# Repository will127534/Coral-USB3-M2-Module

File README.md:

# Coral M.2 Module with USB3 connection with Host

Basically this is a 2242 M.2 Module with VL805 PCIe to USB3 controller connected to Google Coral Module via USB3, because Google Coral TPU still has some issue with the PCIe Driver on Raspberry Pi 4 as of 2022/09.

PCB designed with KiCad v6.0

More details (Blog post?) here: [Coral USB3 M2 Module](https://www.willwhang.dev/coral-USB3-M2-Module/)

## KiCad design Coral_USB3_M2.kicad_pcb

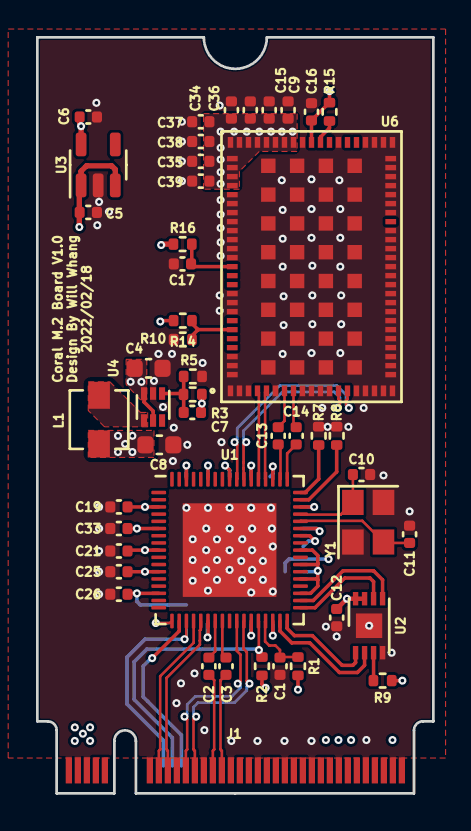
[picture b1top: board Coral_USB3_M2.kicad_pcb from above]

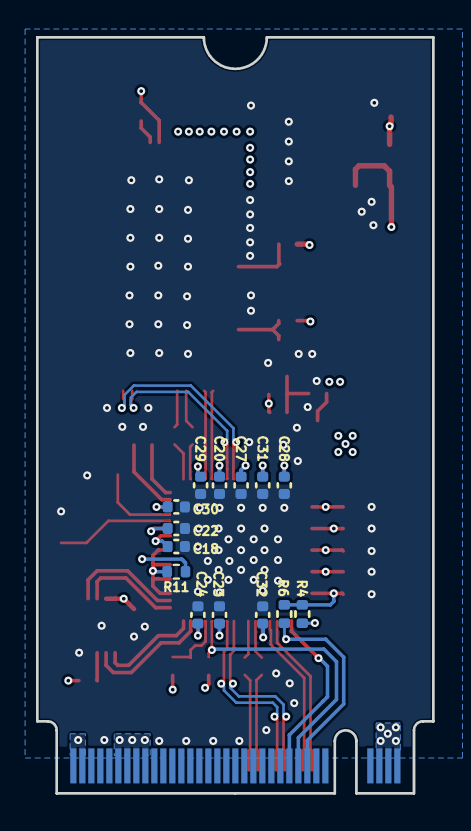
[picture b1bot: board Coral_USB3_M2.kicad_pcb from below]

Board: 4 copper layers, 22.0 x 42.0 mm, 61 parts (14 on the bottom side), 40 nets.

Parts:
C1, C16: 1uF; C_0402_1005Metric
C2, C3, C12, C13, C14, C15, C17, C18, C19, C20, C21, C22, C23, C24, C25, C26, C27, C28, C29, C30, C31, C32, C33, C34, C35, C36, C37, C38, C39: 100nF; C_0402_1005Metric
C4: 10uF; C_0603_1608Metric
C5, C6, C9: 10uF; C_0402_1005Metric
C7: 10pF; C_0402_1005Metric
C8: 22uF; C_0603_1608Metric
C10, C11: 18pF; C_0402_1005Metric
J1: Bus_M.2_Socket_M; NGFF_M
L1: 1uH; L_Vishay_IHLP-1212
R1, R2, R6, R9, R16: 10K; R_0402_1005Metric
R3: 75K; R_0402_1005Metric
R4, R10: DNP; R_0402_1005Metric
R5: 100K; R_0402_1005Metric
R7: 4.7K; R_0402_1005Metric
R8: 6.04K; R_0402_1005Metric
R11: 15K; R_0402_1005Metric
R14: 0R; R_0402_1005Metric
R15: 1K; R_0402_1005Metric
U1: VL805; QFN-68-1EP_8x8mm_P0.4mm_EP5.2x5.2mm
U2: W25Q32JVZP; DFN-8-1EP_3x2mm_P0.5mm_EP1.36x1.46mm
U3: AP2204K-1.8; SOT-23-5
U4: TLV62568ADRLR; SOT-563
U6: G313-06329-00; MODULE_G313-06329-00
Y1: 25Mhz; Crystal_SMD_3225-4Pin_3.2x2.5mm

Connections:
+1V1: C7.1, C8.1, C18.2, C19.2, C21.2, C23.2, C25.2, C27.2, C29.2, C31.2, L1.2, R3.1, U1.3 (VCCA10SSRX34), U1.9 (VDD), U1.12 (VCCA10SSRX34), U1.29 (VDD), U1.45 (VDD), U1.54 (VCCA10SSRX12), U1.60 (VDD), U1.63 (VCCA10SSRX12)
+1V8: C6.1, C16.1, R14.2, R15.2, R16.1, U3.5 (VOUT), U6.54 (AON)
+3.3VA: C4.2, C5.1, C9.1, C12.2, C15.1, C20.2, C22.2, C24.2, C26.2, C28.2, C30.2, C32.2, C33.2, C34.2, C35.2, C36.2, C37.2, C38.2, C39.2, J1.2 (3.3V), J1.4 (3.3V), J1.12 (3.3V), J1.14 (3.3V), J1.16 (3.3V), J1.18 (3.3V), J1.70 (3.3V), J1.72 (3.3V), J1.74 (3.3V), R1.2, R2.2, R4.2, R6.2, R9.1, R11.2, U1.6 (VCCA33SS34), U1.15 (VCCA33SS34), U1.23 (VCCA33PEX), U1.32 (VSUS33), U1.46 (VSUS33), U1.49 (VCCA33SSM), U1.57 (VCCA33SS12), U1.66 (VCCA33SS12), U2.7 (IO3), U2.8 (VCC), U3.1 (VIN), U3.3 (EN), U4.3 (VIN), U4.5 (EN), U6.56 (VIN), U6.57 (VIN), U6.58 (VIN), U6.59 (VIN), U6.60 (VIN), U6.61 (VIN), U6.62 (VIN), U6.63 (VIN), U6.64 (VIN), U6.65 (VIN), U6.66 (VIN), U6.67 (VIN)
GND: C1.1, C4.1, C5.2, C6.2, C8.2, C9.2, C10.1, C11.1, C12.1, C15.2, C16.2, C17.2, C18.1, C19.1, C20.1, C21.1, C22.1, C23.1, C24.1, C25.1, C26.1, C27.1, C28.1, C29.1, C30.1, C31.1, C32.1, C33.1, C34.1, C35.1, C36.1, C37.1, C38.1, C39.1, J1.1 (GND), J1.3 (GND), J1.9 (GND), J1.15 (GND), J1.21 (GND), J1.27 (GND), J1.33 (GND), J1.39 (GND), J1.45 (GND), J1.51 (GND), J1.57 (GND), J1.71 (GND), J1.73 (GND), J1.75 (GND), R5.2, R7.1, R8.1, R10.1, U1.69 (GND), U2.4 (GND), U2.9 (EP), U3.2 (GND), U4.2 (GND), U6.1 (GND), U6.2 (GND), U6.3 (GND), U6.6 (GND), U6.9 (GND), U6.10 (PCIE_REFCLK_N), U6.11 (PCIE_REFCLK_P), U6.12 (GND), U6.15 (GND), U6.16 (GND), U6.17 (GND), U6.18 (GND), U6.19 (GND), U6.20 (GND), U6.21 (GND), U6.22 (GND), U6.23 (GND), U6.24 (GND), U6.25 (GND), U6.26 (GND), U6.27 (GND), U6.28 (GND), U6.29 (GND), U6.30 (GND), U6.31 (GND), U6.32 (GND), U6.33 (GND), U6.34 (GND), U6.35 (GND), U6.36 (GND), U6.38 (GND), U6.39 (GND), U6.40 (GND), U6.41 (GND), U6.42 (GND), U6.43 (GND), U6.44 (GND), U6.45 (GND), U6.46 (GND), U6.47 (GND), U6.48 (GND), U6.51 (GND), U6.55 (GND), U6.68 (GND), U6.69 (GND), U6.70 (GND), U6.71 (GND), U6.72 (GND), U6.73 (GND), U6.74 (GND), U6.75 (GND), U6.79 (GND), U6.80 (GND), U6.81 (GND), U6.86 (GND), U6.87 (GND), U6.88 (GND), U6.89 (GND), U6.90 (GND), U6.91 (GND), U6.92 (GND), U6.93 (GND), U6.94 (GND), U6.95 (GND), U6.96 (GND), U6.97 (GND), U6.98 (GND), U6.99 (GND), U6.100 (GND), U6.101 (GND), U6.102 (GND), U6.103 (GND), U6.104 (GND), U6.105 (GND), U6.106 (GND), U6.107 (GND), U6.108 (GND), U6.109 (GND), U6.110 (GND), U6.111 (GND), U6.112 (GND), U6.113 (GND), U6.114 (GND), U6.115 (GND), U6.116 (GND), U6.117 (GND), U6.118 (GND), U6.119 (GND), U6.120 (GND), Y1.2, Y1.4
unnamed: C1.2, R1.1, U1.31 (~PONRST)
unnamed: C2.2, U1.24 (PE_TXP)
unnamed: C3.2, U1.25 (PE_TXN)
unnamed: C7.2, R3.2, R5.1, U4.1 (FB)
unnamed: C10.2, U1.48 (XO), Y1.1
unnamed: C11.2, U1.47 (XI), Y1.3
unnamed: C13.2, U6.7 (PCIE_RX_P)
unnamed: C14.2, U6.8 (PCIE_RX_N)
unnamed: L1.1, U4.4 (SW)
unnamed: R7.2, U1.51 (TESTEN)
unnamed: R8.2, U1.50 (SSREXT)
unnamed: R9.2, U2.3 (IO2)
unnamed: R11.1, U1.37 (~USBHOC4), U1.39 (~USBHOC3), U1.41 (~USBHOC2), U1.43 (~USBHOC1)
unnamed: R15.1, U6.53 (PMIC_EN)
unnamed: U1.33 (SPI_DO), U2.2 (DO(IO1))
unnamed: U1.34 (SPI_CS), U2.1 (~CS)
unnamed: U1.35 (SPI_CLK), U2.6 (CLK)
unnamed: U1.36 (SPI_DI), U2.5 (DI(IO0))
PCIe_CLK_N: J1.53 (REFCLKn), U1.22 (PE_CLKN)
PCIe_CLK_P: J1.55 (REFCLKp), U1.21 (PE_CLKP)
PCIe_CLK_REQ: J1.52 (~CLKREQ), R2.1, U1.30 (~PE_CLKREQ)
PCIe_RST: J1.50 (~PERST), U1.19 (~PE_RST)
PCIe_RX_N: C2.1, J1.43 (PERp0/SATA-B-)
PCIe_RX_P: C3.1, J1.41 (PERn0/SATA-B+)
PCIe_TX_N: J1.49 (PETp0/SATA-A+), U1.27 (PE_RXP)
PCIe_TX_P: J1.47 (PETn0/SATA-A-), U1.28 (PE_RXN)
PE_WAKE: J1.54 (~PEWAKE), R6.1, U1.20 (~PE_WAKE)
SMI: R4.1, U1.18 (~SMI)
TPU_RST: C17.1, R16.2, U6.76 (RST_L)
TPU_USB_SEL: R10.2, R14.1, U6.83 (USB_SEL)
USB3_RX1+: U1.55 (SSRX1+), U6.5 (PCIE_TX_P)
USB3_RX1-: U1.56 (SSRX1-), U6.4 (PCIE_TX_N)
USB3_TX1+: C14.1, U1.52 (SSTX1+)
USB3_TX1-: C13.1, U1.53 (SSTX1-)
USB_TPU1_DN: U1.59 (USB2D1-), U6.14 (USB2_D_N)
USB_TPU1_DP: U1.58 (USB2D1+), U6.13 (USB2_D_P)

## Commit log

2022-09-25 init
2022-09-25 Init page
2022-09-25 edit page
2022-09-25 Comment from will on index
2022-09-25 Remove test comment
2022-10-19 Adding Coral Compatibility Test Suite pass result
2024-07-07 Fix link for the blog post
